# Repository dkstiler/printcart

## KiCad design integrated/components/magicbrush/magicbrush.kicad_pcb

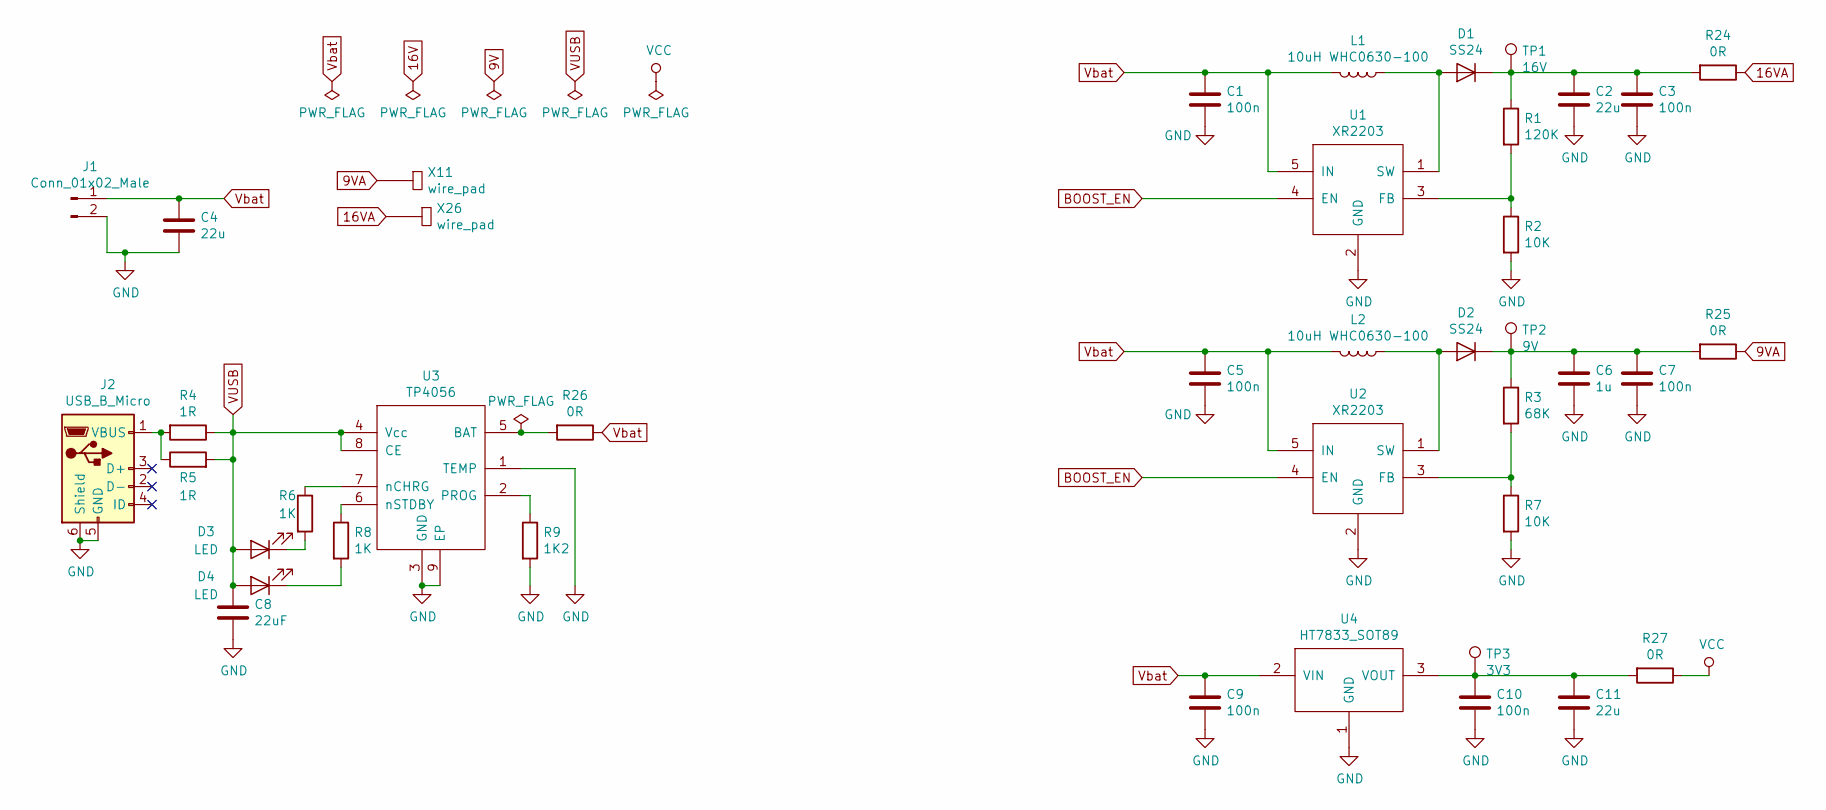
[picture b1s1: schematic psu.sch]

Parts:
C1, C3, C5, C7, C9, C10: 100n; C_0603_1608Metric_Pad1.05x0.95mm_HandSolder
C2, C4, C11: 22u; C_0805_2012Metric_Pad1.15x1.40mm_HandSolder
C6: 1u; C_0603_1608Metric_Pad1.05x0.95mm_HandSolder
C8: 22uF; C_0805_2012Metric_Pad1.15x1.40mm_HandSolder
D1, D2: SS24; D_SMB_Handsoldering
D3, D4: LED; LED_0603_1608Metric_Pad1.05x0.95mm_HandSolder
J1: Conn_01x02_Male; PinHeader_1x02_P2.54mm_Vertical
J2: USB_B_Micro; USB_Micro-B_0.8mm_taobao
L1, L2: 10uH WHC0630-100; IND_WHC0630
R1: 120K; R_0603_1608Metric
R2, R7: 10K; R_0603_1608Metric
R3: 68K; R_0603_1608Metric
R4, R5: 1R; R_0603_1608Metric
R6, R8: 1K; R_0603_1608Metric
R9: 1K2; R_0603_1608Metric
R24, R25, R26, R27: 0R; R_0603_1608Metric_Pad1.05x0.95mm_HandSolder
TP1: 16V; TestPoint_Pad_D1.5mm
TP2: 9V; TestPoint_Pad_D1.5mm
TP3: 3V3; TestPoint_Pad_D1.5mm
U1, U2: XR2203; SOT-23-5
U3: TP4056; SOIC-8-1EP_3.9x4.9mm_P1.27mm_EP2.35x2.35mm
U4: HT7833_SOT89; SOT-89-3
X11, X26: wire_pad; wire_pad_1mm

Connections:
9VA: R25.1, X11.1
16VA: R24.1, X26.1
BOOST_EN: U1.4 (EN), U2.4 (EN); also elsewhere on the board
unnamed: C2.1, C3.1, D1.1 (K), R1.1, R24.2, TP1.1
unnamed: C6.1, C7.1, D2.1 (K), R3.1, R25.2, TP2.1
unnamed: C10.1, C11.1, R27.2, TP3.1, U4.3 (VOUT)
unnamed: D1.2 (A), L1.1, U1.1 (SW)
unnamed: D2.2 (A), L2.1, U2.1 (SW)
unnamed: D3.1 (K), R6.2
unnamed: D4.1 (K), R8.2
unnamed: J2.1 (VBUS), R4.2, R5.1
unnamed: R1.2, R2.1, U1.3 (FB)
unnamed: R3.2, R7.1, U2.3 (FB)
unnamed: R6.1, U3.7 (nCHRG)
unnamed: R8.1, U3.6 (nSTDBY)
unnamed: R9.1, U3.2 (PROG)
unnamed: R26.2, U3.5 (BAT)
VCC: R27.1; also elsewhere on the board
VUSB: C8.1, D3.2 (A), D4.2 (A), R4.1, R5.2, U3.4 (Vcc), U3.8 (CE)
Vbat: C1.1, C4.1, C5.1, C9.1, J1.1, L1.2, L2.2, R26.1, U1.5 (IN), U2.5 (IN), U4.2 (VIN); also elsewhere on the board

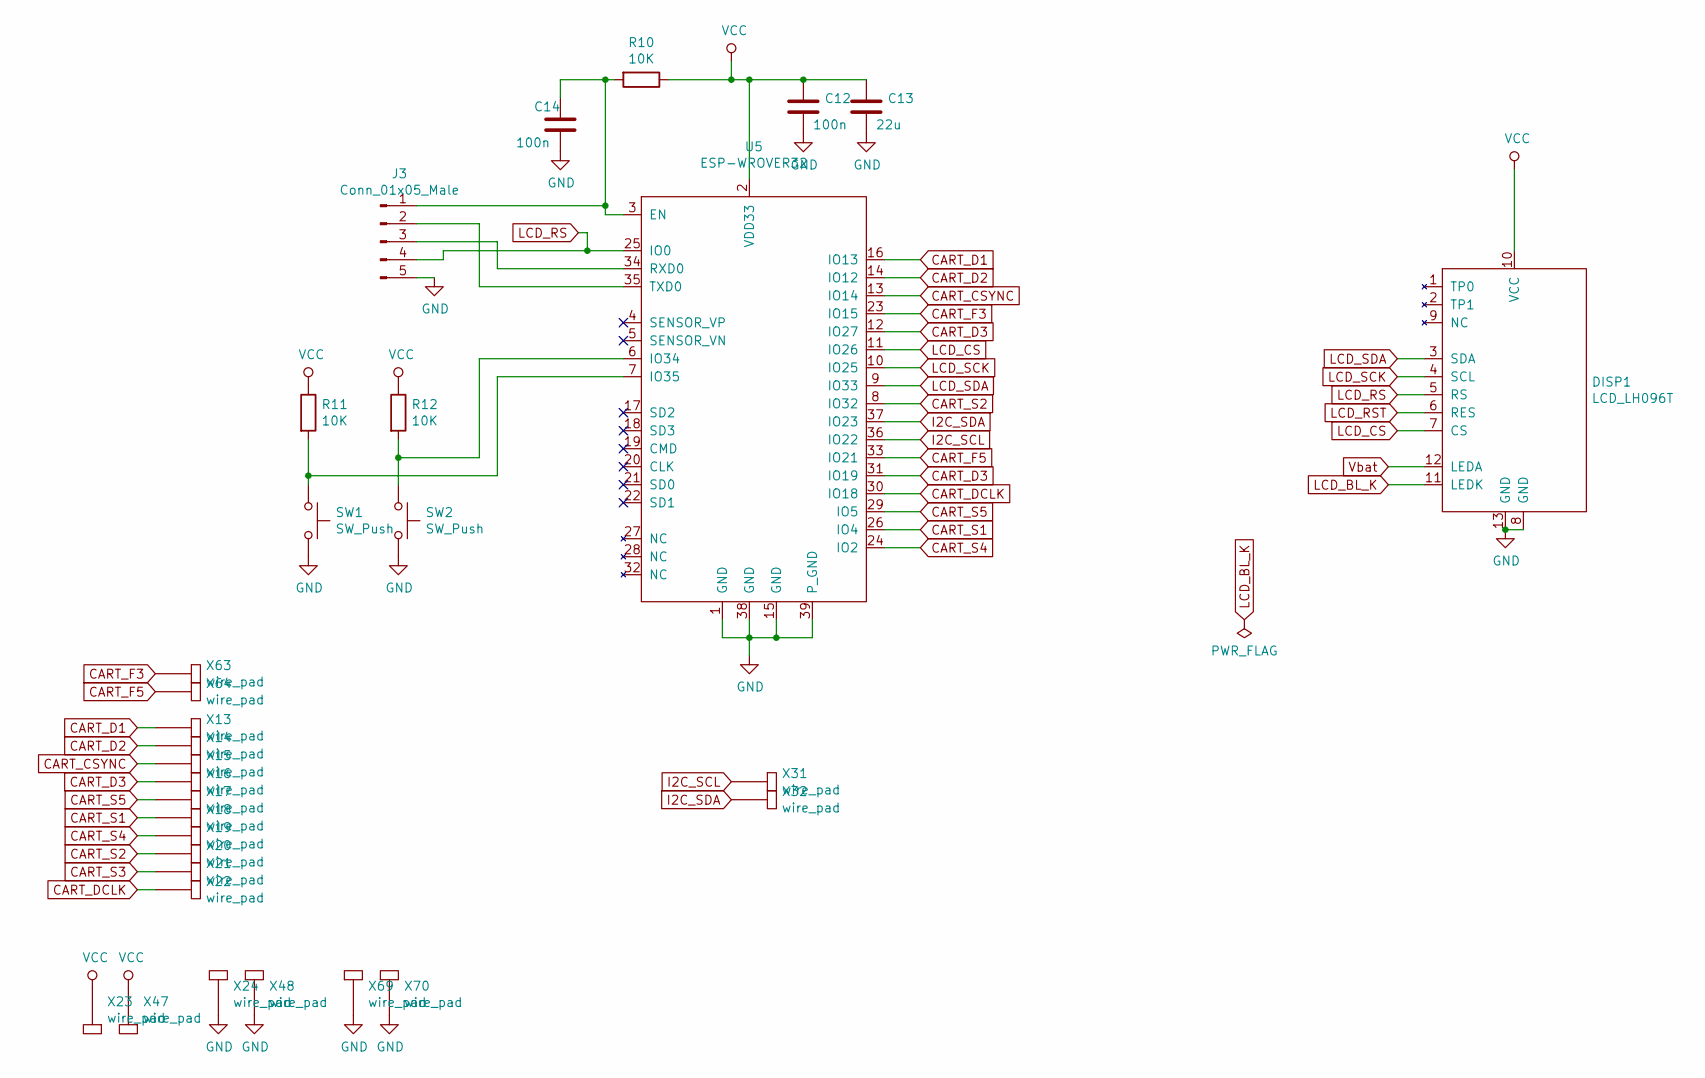
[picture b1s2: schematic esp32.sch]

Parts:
C12, C14: 100n; C_0603_1608Metric_Pad1.05x0.95mm_HandSolder
C13: 22u; C_0805_2012Metric_Pad1.15x1.40mm_HandSolder
DISP1: LCD_LH096T; LCD_LH086T
J3: Conn_01x05_Male; PinHeader_1x05_P2.54mm_Vertical
R10, R11, R12: 10K; R_0603_1608Metric
SW1, SW2: SW_Push; SW_PUSH_6mm
U5: ESP-WROVER32; ESP-WROVER-MOD
X13, X14, X15, X16, X17, X18, X19, X20, X21, X22, X31, X32, X63, X64: wire_pad; wire_pad_0.5mm
X23, X24, X47, X48, X69, X70: wire_pad; wire_pad_1mm

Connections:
CART_CSYNC: U5.13 (IO14), X15.1; also elsewhere on the board
CART_D1: U5.16 (IO13), X13.1; also elsewhere on the board
CART_D2: U5.14 (IO12), X14.1; also elsewhere on the board
CART_DCLK: U5.30 (IO18), X22.1; also elsewhere on the board
CART_F3: U5.23 (IO15), X63.1; also elsewhere on the board
CART_F5: U5.33 (IO21), X64.1; also elsewhere on the board
CART_S1: U5.26 (IO4), X18.1; also elsewhere on the board
CART_S2: U5.8 (IO32), X20.1; also elsewhere on the board
CART_S4: U5.24 (IO2), X19.1; also elsewhere on the board
CART_S5: U5.29 (IO5), X17.1; also elsewhere on the board
I2C_SCL: U5.36 (IO22), X31.1; also elsewhere on the board
I2C_SDA: U5.37 (IO23), X32.1; also elsewhere on the board
LCD_BL_K: DISP1.11 (LEDK); also elsewhere on the board
LCD_CS: DISP1.7 (CS), U5.11 (IO26)
LCD_RS: DISP1.5 (RS), J3.4, U5.25 (IO0)
LCD_RST: DISP1.6 (RES); also elsewhere on the board
LCD_SCK: DISP1.4 (SCL), U5.10 (IO25)
LCD_SDA: DISP1.3 (SDA), U5.9 (IO33)
unnamed: C14.1, J3.1, R10.2, U5.3 (EN)
unnamed: J3.2, U5.35 (TXD0)
unnamed: J3.3, U5.34 (RXD0)
unnamed: R11.2, SW1.1, U5.7 (IO35)
unnamed: R12.2, SW2.1, U5.6 (IO34)
VCC: C12.1, C13.1, DISP1.10 (VCC), R10.1, R11.1, R12.1, U5.2 (VDD33), X23.1, X47.1; also elsewhere on the board
Vbat: DISP1.12 (LEDA); also elsewhere on the board

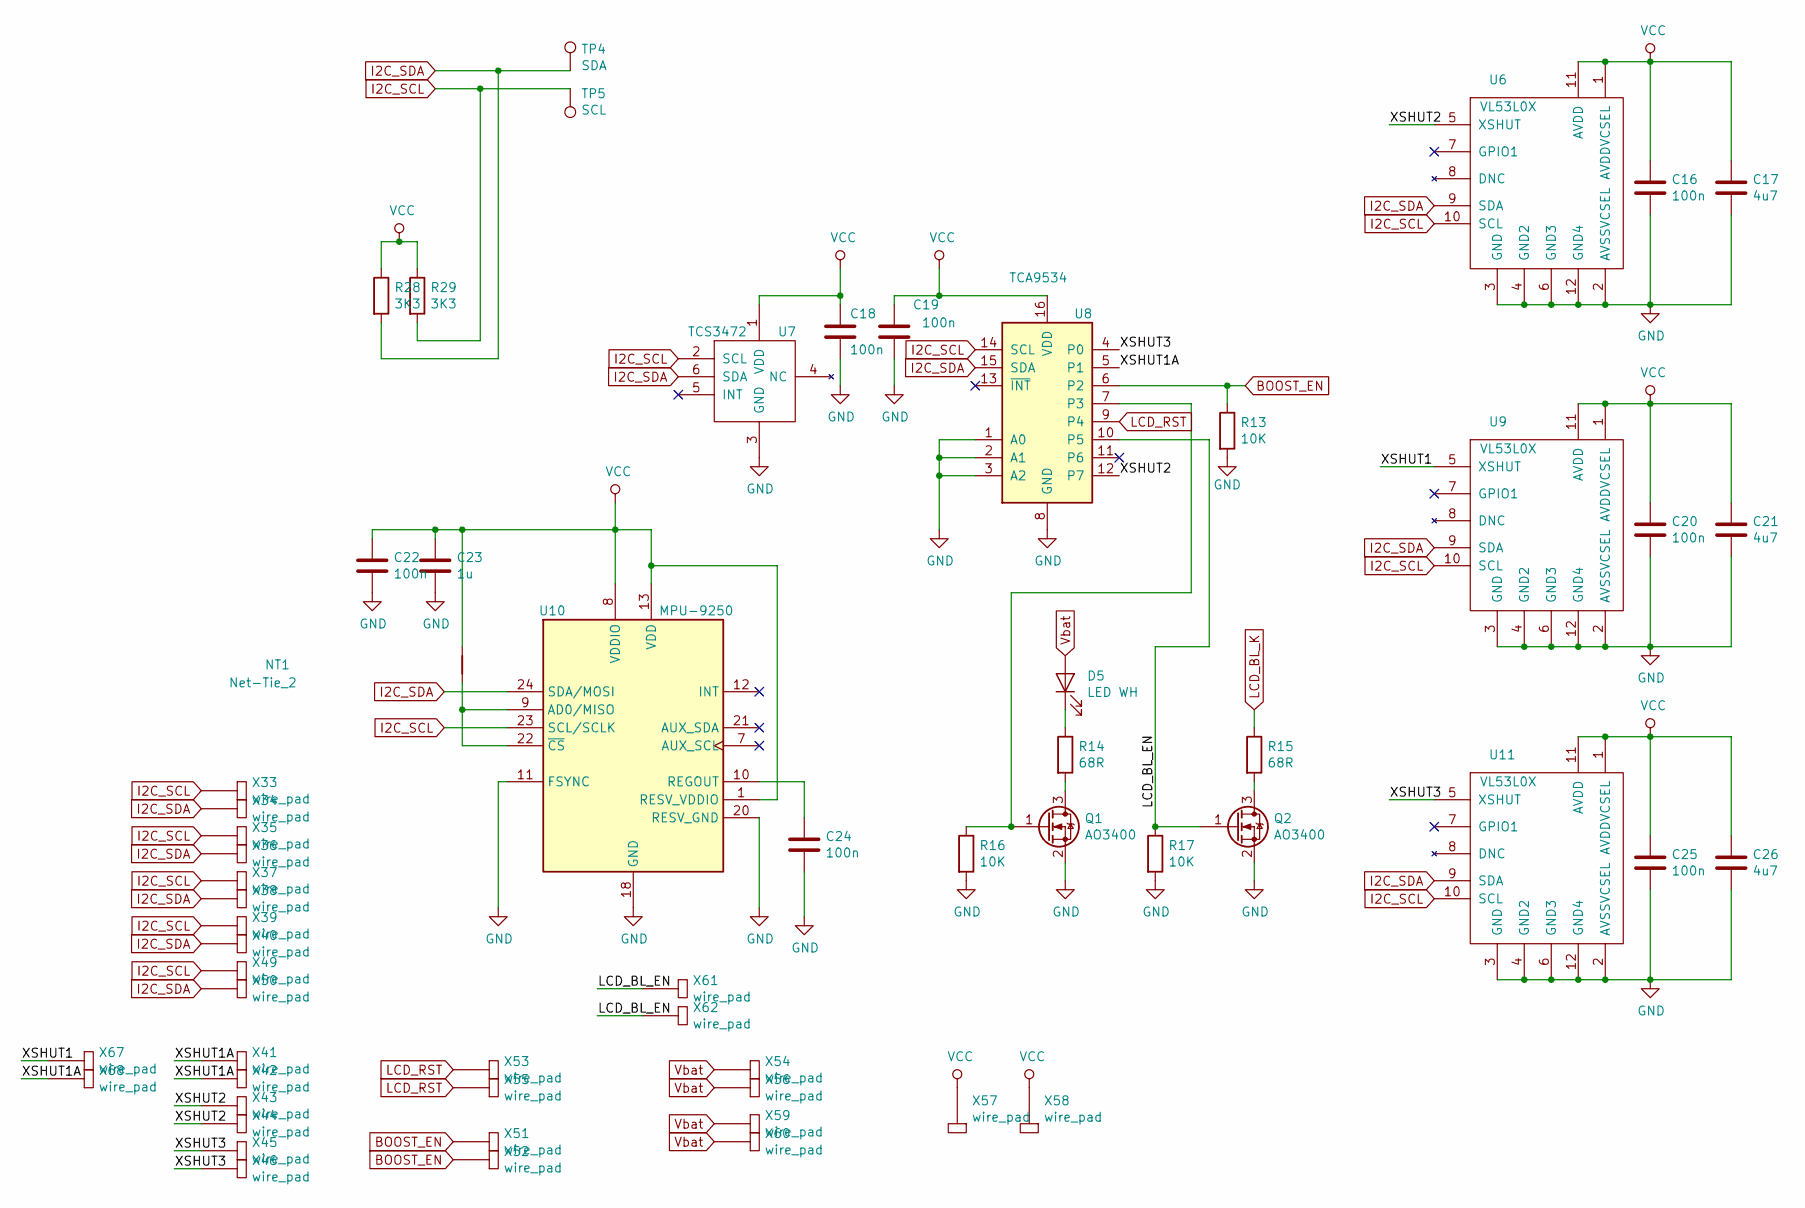
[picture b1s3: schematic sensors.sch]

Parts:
C16, C18, C19, C20, C22, C24, C25: 100n; C_0603_1608Metric_Pad1.05x0.95mm_HandSolder
C17, C21, C26: 4u7; C_0805_2012Metric_Pad1.15x1.40mm_HandSolder
C23: 1u; C_0603_1608Metric_Pad1.05x0.95mm_HandSolder
D5: LED WH; LED_0603_1608Metric_Pad1.05x0.95mm_HandSolder
NT1: Net-Tie_2; NetTie-2_THT_Pad0.3mm
Q1, Q2: AO3400; SOT-23
R13, R16, R17: 10K; R_0603_1608Metric
R14, R15: 68R; R_0603_1608Metric
R28, R29: 3K3; R_0603_1608Metric
TP4: SDA; TestPoint_Pad_D1.5mm
TP5: SCL; TestPoint_Pad_D1.5mm
U6, U9, U11: VL53L0X; VL53LxX
U7: TCS3472; DFNL_FN_TCS3472
U8: TCA9534; TSSOP-16_4.4x5mm_P0.65mm
U10: MPU-9250; QFN-24_3x3mm_P0.4mm
X33, X34, X35, X36, X37, X38, X39, X40, X41, X42, X43, X44, X45, X46, X49, X50, X51, X52, X53, X54, X55, X56, X59, X60, X61, X62, X67, X68: wire_pad; wire_pad_0.5mm
X57, X58: wire_pad; wire_pad_1mm

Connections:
/Sensors/LCD_BL_EN: Q2.1 (G), R17.1, U8.10 (P5), X61.1, X62.1
/Sensors/XSHUT1: U9.5 (XSHUT), X67.1
/Sensors/XSHUT1A: U8.5 (P1), X41.1, X42.1, X68.1
/Sensors/XSHUT2: U6.5 (XSHUT), U8.12 (P7), X43.1, X44.1
/Sensors/XSHUT3: U8.4 (P0), U11.5 (XSHUT), X45.1, X46.1
BOOST_EN: R13.1, U8.6 (P2), X51.1, X52.1; also elsewhere on the board
I2C_SCL: R29.2, TP5.1, U6.10 (SCL), U7.2 (SCL), U8.14 (SCL), U9.10 (SCL), U10.23 (SCL/SCLK), U11.10 (SCL), X33.1, X35.1, X37.1, X39.1, X49.1; also elsewhere on the board
I2C_SDA: R28.2, TP4.1, U6.9 (SDA), U7.6 (SDA), U8.15 (SDA), U9.9 (SDA), U10.24 (SDA/MOSI), U11.9 (SDA), X34.1, X36.1, X38.1, X40.1, X50.1; also elsewhere on the board
LCD_BL_K: R15.1; also elsewhere on the board
LCD_RST: U8.9 (P4), X53.1, X55.1; also elsewhere on the board
unnamed: C24.1, U10.10 (REGOUT)
unnamed: D5.1 (K), R14.1
unnamed: NT1.2, U10.9 (AD0/MISO), U10.22 (~CS)
unnamed: Q1.1 (G), R16.1, U8.7 (P3)
unnamed: Q1.3 (D), R14.2
unnamed: Q2.3 (D), R15.2
VCC: C16.1, C17.1, C18.1, C19.1, C20.1, C21.1, C22.1, C23.1, C25.1, C26.1, NT1.1, R28.1, R29.1, U6.1 (AVDDVCSEL), U6.11 (AVDD), U7.1 (VDD), U8.16 (VDD), U9.1 (AVDDVCSEL), U9.11 (AVDD), U10.1 (RESV_VDDIO), U10.8 (VDDIO), U10.13 (VDD), U11.1 (AVDDVCSEL), U11.11 (AVDD), X57.1, X58.1; also elsewhere on the board
Vbat: D5.2 (A), X54.1, X56.1, X59.1, X60.1; also elsewhere on the board

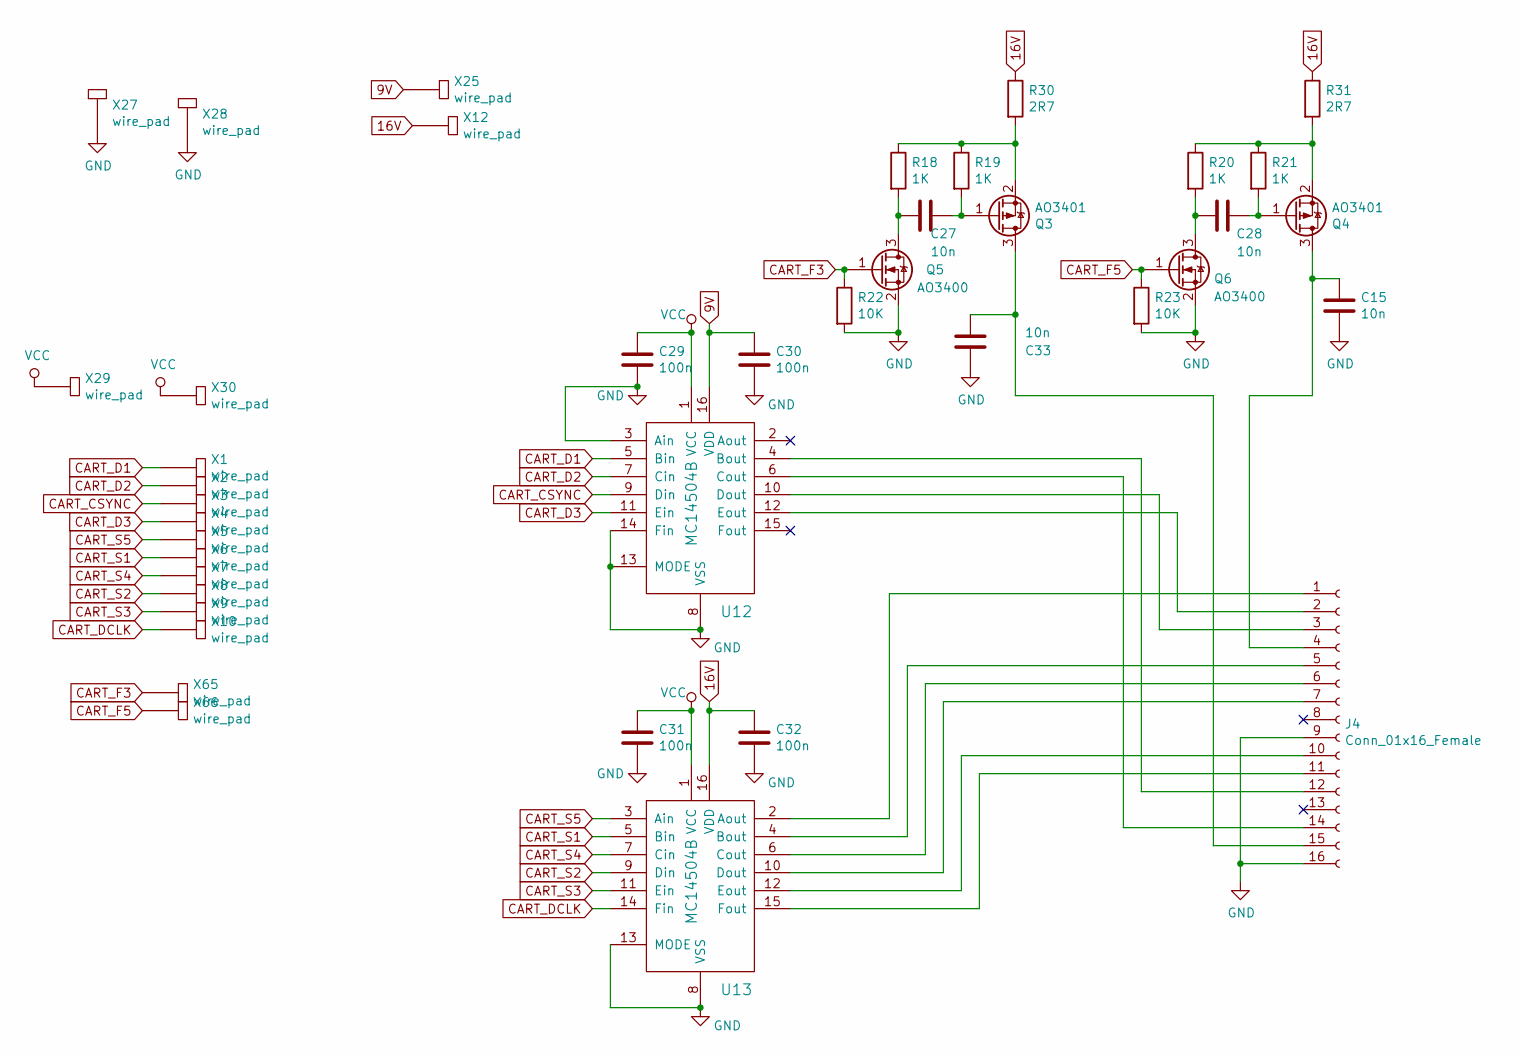
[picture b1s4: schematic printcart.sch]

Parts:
C15, C27, C28, C33: 10n; C_0603_1608Metric_Pad1.05x0.95mm_HandSolder
C29, C30, C31, C32: 100n; C_0603_1608Metric_Pad1.05x0.95mm_HandSolder
J4: Conn_01x16_Female; HP_803_CART
Q3, Q4: AO3401; SOT-23
Q5, Q6: AO3400; SOT-23
R18, R19, R20, R21: 1K; R_0603_1608Metric
R22, R23: 10K; R_0603_1608Metric
R30, R31: 2R7; R_0603_1608Metric
U12, U13: MC14504B; SOIC-16_3.9x9.9mm_P1.27mm
X1, X2, X3, X4, X5, X6, X7, X8, X9, X10, X65, X66: wire_pad; wire_pad_0.5mm
X12, X25, X27, X28, X29, X30: wire_pad; wire_pad_1mm

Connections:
9V: C30.1, U12.16 (VDD), X25.1
16V: C32.1, R30.1, R31.1, U13.16 (VDD), X12.1
CART_CSYNC: U12.9 (Din), X3.1; also elsewhere on the board
CART_D1: U12.5 (Bin), X1.1; also elsewhere on the board
CART_D2: U12.7 (Cin), X2.1; also elsewhere on the board
CART_DCLK: U13.14 (Fin), X10.1; also elsewhere on the board
CART_F3: Q5.1 (G), R22.1, X65.1; also elsewhere on the board
CART_F5: Q6.1 (G), R23.1, X66.1; also elsewhere on the board
CART_S1: U13.5 (Bin), X6.1; also elsewhere on the board
CART_S2: U13.9 (Din), X8.1; also elsewhere on the board
CART_S4: U13.7 (Cin), X7.1; also elsewhere on the board
CART_S5: U13.3 (Ain), X5.1; also elsewhere on the board
unnamed: C15.1, J4.4, Q4.3 (D)
unnamed: C27.1, Q3.1 (G), R19.2
unnamed: C27.2, Q5.3 (D), R18.2
unnamed: C28.1, Q4.1 (G), R21.2
unnamed: C28.2, Q6.3 (D), R20.2
unnamed: J4.1, U13.2 (Aout)
unnamed: J4.2, U12.12 (Eout)
unnamed: J4.3, U12.10 (Dout)
unnamed: J4.5, U13.4 (Bout)
unnamed: J4.6, U13.6 (Cout)
unnamed: J4.7, U13.10 (Dout)
unnamed: J4.10, U13.12 (Eout)
unnamed: J4.11, U13.15 (Fout)
unnamed: J4.12, U12.4 (Bout)
unnamed: J4.14, U12.6 (Cout)
unnamed: Q3.2 (S), R18.1, R19.1, R30.2
unnamed: Q4.2 (S), R20.1, R21.1, R31.2
VCC: C29.1, C31.1, U12.1 (VCC), U13.1 (VCC), X29.1, X30.1; also elsewhere on the board

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
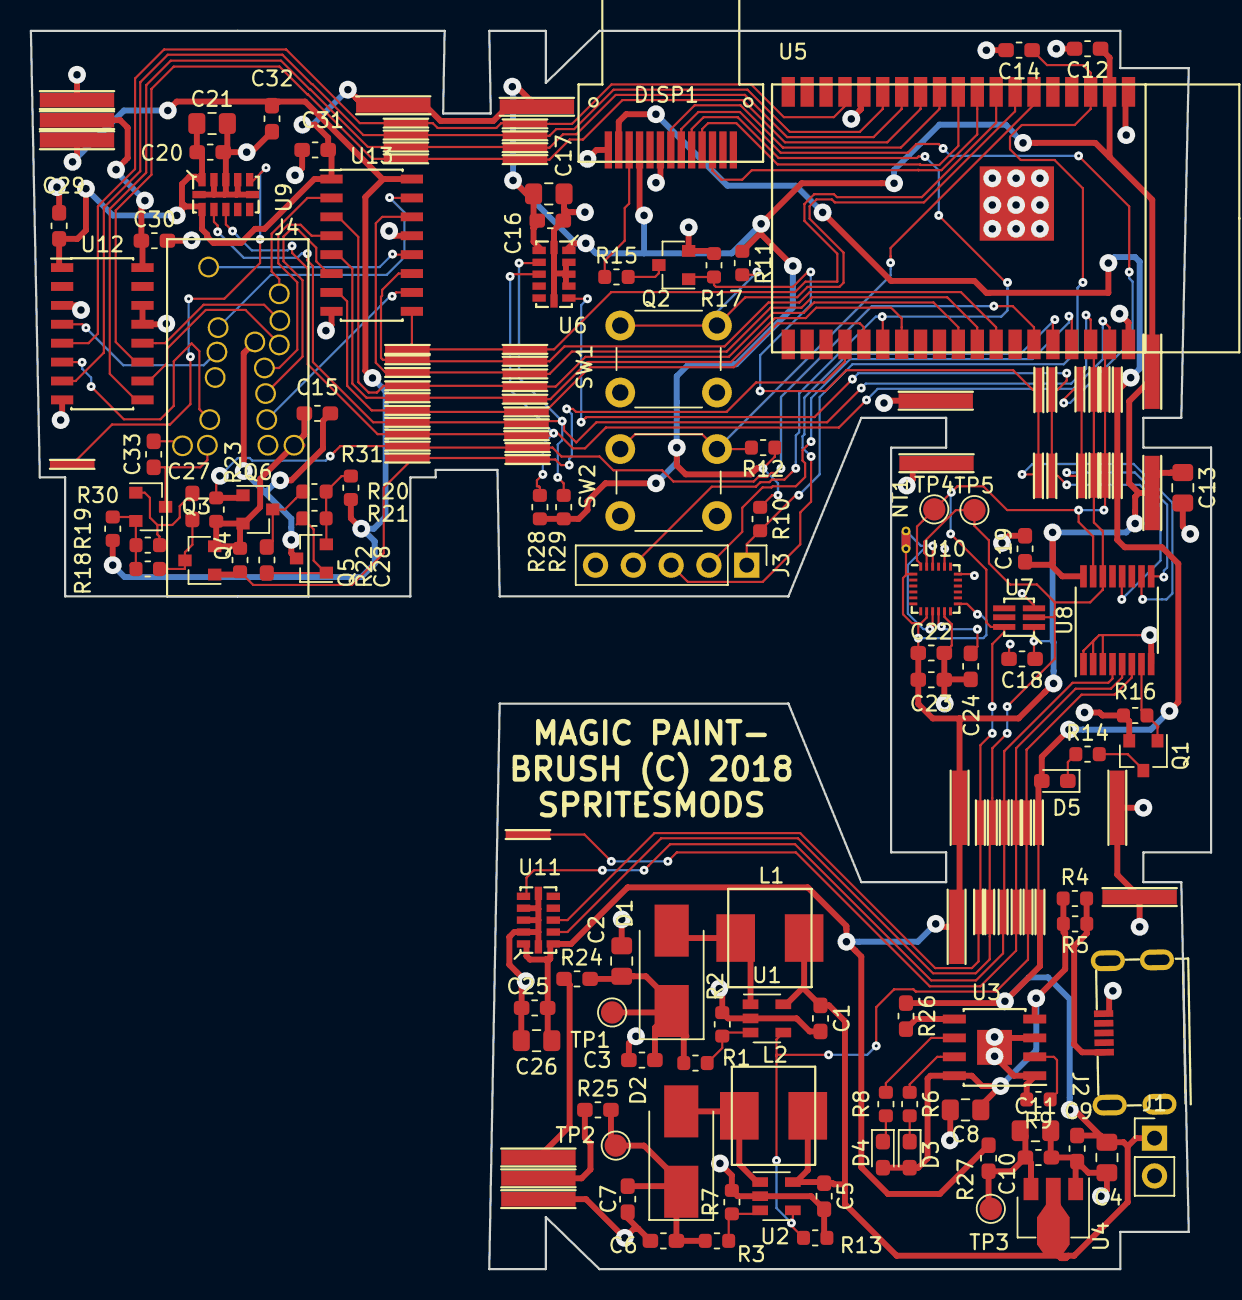
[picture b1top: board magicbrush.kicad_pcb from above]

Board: 2 copper layers, 79.3 x 83.2 mm, 173 parts (0 on the bottom side), 77 nets.

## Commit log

2018-05-01 Initial commit. Wave shaper html thing only for now.
2018-05-27 More-or-less works. Need more speed.
2018-06-07 Add waveform decoding tests
2018-06-08 Make and broke wfmdec...
2018-06-08 Aaand fixed.
2018-06-08 It decodes!
2018-06-10 Wfmdec: un-frazzle bit-order. ESP32: encode graphics now
2018-06-10 Getting there!
2018-09-09 Move stuff
2018-09-09 make decode script cmy
2018-09-10 Add ltr/rtl mode differences
2018-09-10 Figured out power use, more notes
2018-09-11 Kinda works, but middle nozzles are not very enthousiastic...
2018-09-14 IT PRINTS!!!!
2018-09-14 Better nozzle thing
2018-09-14 IT WORKS! Sooo happy. The Nyancat prints.
2018-09-24 Algo test
2018-09-26 Kinda-sorta works... inprecise though
2018-09-29 Lalatest
2018-10-01 Rx works but timing is shit
2018-10-16 New notes, dump US bit
2018-10-19 Add integrated PCB firmware. Distance sensor, LCD, color sensor, MPU all work.
2018-10-20 All sensors work.
2018-10-24 Broken :/
2018-10-27 Added webserver to nyancat test; finally fix waveform to work on portable unit as well
2018-10-27 Integrated also spits out ink now.
2018-11-01 Final update: lots of hackery to get some quick and dirty effects going.
2018-11-17 Attempt at IMU/ToF magic; wfmdec decodes black cartridges as well
2018-11-18 Add b/w cart support (hackish, needs different wf for now that needs editing of sources). Still some pixel order issues, but nothing major.
2018-12-11 Cleanup
2025-09-18 add pcb files

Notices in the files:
integrated/components/magicbrush/magicbrush.kicad_pcb:
BRUSH (C) 2018
